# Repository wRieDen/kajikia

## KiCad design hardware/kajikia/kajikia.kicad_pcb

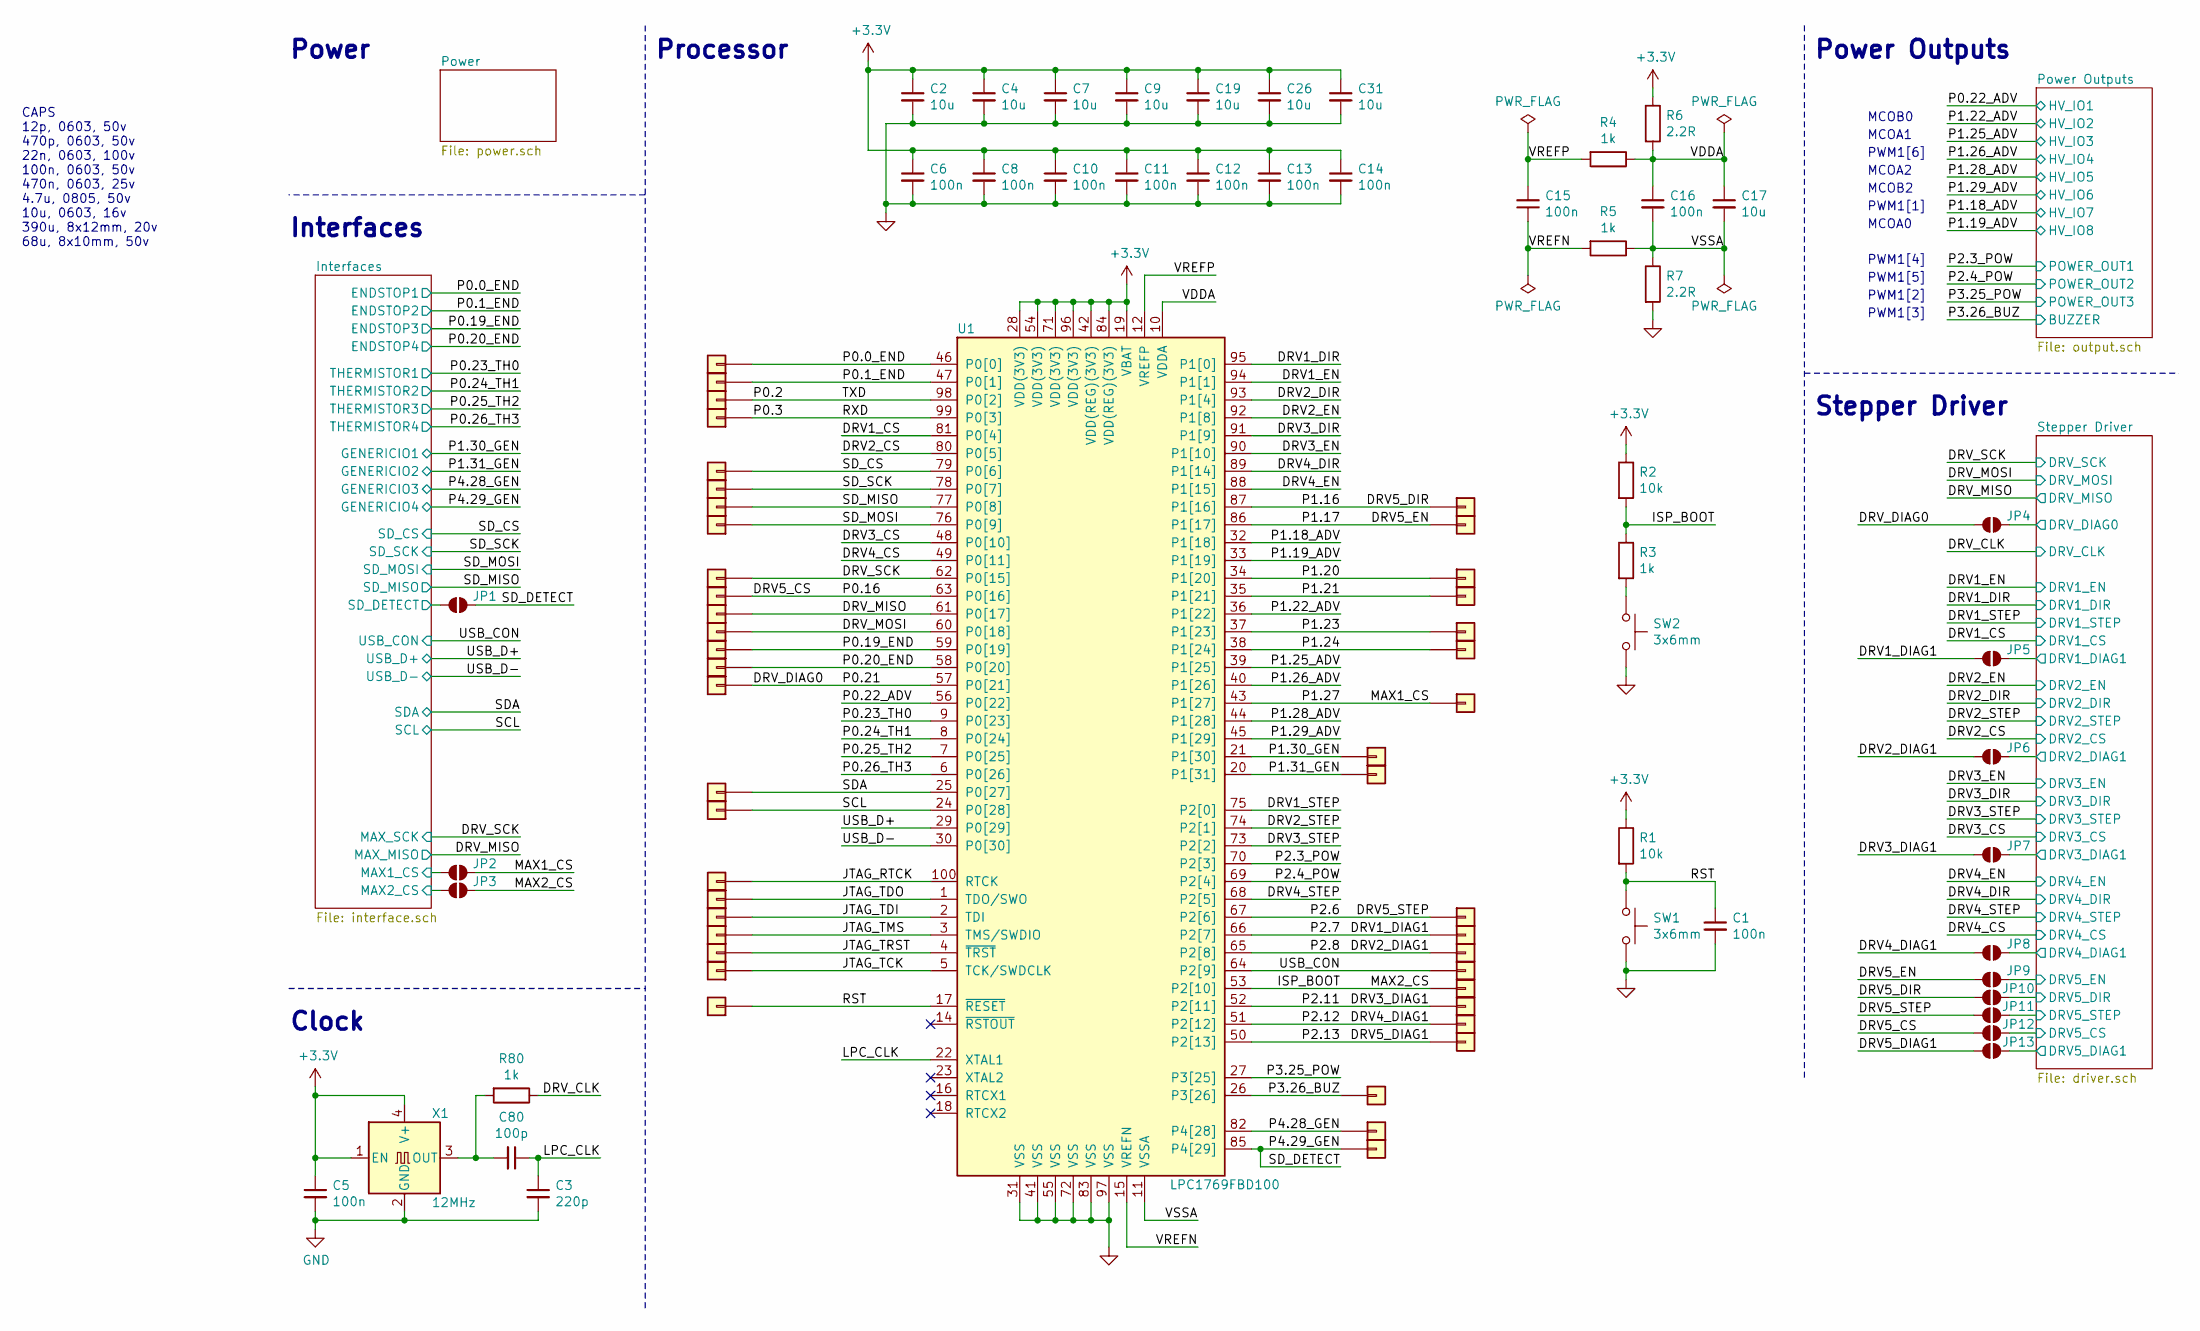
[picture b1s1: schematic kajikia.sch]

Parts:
C1, C5, C6, C8, C10, C11, C12, C13, C14, C15, C16: 100n; 0603_CAP
C2, C4, C7, C9, C17, C19, C26, C31: 10u; 0603_CAP
C3: 220p; 0603_CAP
C80: 100p; 0603_CAP
J1, J2, J3, J4, J5, J6, J7, J8, J9, J10, J11, J12, J13, J14, J15, J16, J17, J18, J19, J20, J21, J22, J23, J24, J25, J26, J27, J28, J29, J30, J31, J32, J33, J34, J35, J36, J37, J38, J52, J75, J76, J77, J78, J104: Conn_01x01; PinHeader_2.54mm_1P
JP1, JP2, JP3, JP4, JP5, JP6, JP7, JP8, JP9, JP10, JP11, JP12, JP13: SolderJumper_2_Open; Solder Jumper 2P
R1, R2: 10k; 0603_RES
R3, R4, R5, R80: 1k; 0603_RES
R6, R7: 2.2R; 0603_RES
SW1, SW2: 3x6mm; Switch_3x4mm
U1: LPC1769FBD100; LQFP-100_14x14mm_P0.5mm
X1: 12MHz; Oscillator_SMD_EuroQuartz_XO32-4Pin_3.2x2.5mm

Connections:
+3V3: C2.1, C4.1, C5.1, C6.1, C7.1, C8.1, C9.1, C10.1, C11.1, C12.1, C13.1, C14.1, C19.1, C26.1, C31.1, R1.1, R2.1, R6.1, U1.19 (VBAT), U1.28 (VDD(3V3)), U1.42 (VDD(REG)(3V3)), U1.54 (VDD(3V3)), U1.71 (VDD(3V3)), U1.84 (VDD(REG)(3V3)), U1.96 (VDD(3V3)), X1.1 (EN), X1.4 (V+); also elsewhere on the board
/DRV1_CS: U1.81 (P0[4]); also elsewhere on the board
/DRV1_DIAG1: J33.1, JP5.1 (A), U1.66 (P2[7])
/DRV1_DIR: U1.95 (P1[0]); also elsewhere on the board
/DRV1_EN: U1.94 (P1[1]); also elsewhere on the board
/DRV1_STEP: U1.75 (P2[0]); also elsewhere on the board
/DRV2_CS: U1.80 (P0[5]); also elsewhere on the board
/DRV2_DIAG1: J34.1, JP6.1 (A), U1.65 (P2[8])
/DRV2_DIR: U1.93 (P1[4]); also elsewhere on the board
/DRV2_EN: U1.92 (P1[8]); also elsewhere on the board
/DRV2_STEP: U1.74 (P2[1]); also elsewhere on the board
/DRV3_CS: U1.48 (P0[10]); also elsewhere on the board
/DRV3_DIAG1: J36.1, JP7.1 (A), U1.52 (P2[11])
/DRV3_DIR: U1.91 (P1[9]); also elsewhere on the board
/DRV3_EN: U1.90 (P1[10]); also elsewhere on the board
/DRV3_STEP: U1.73 (P2[2]); also elsewhere on the board
/DRV4_CS: U1.49 (P0[11]); also elsewhere on the board
/DRV4_DIAG1: J37.1, JP8.1 (A), U1.51 (P2[12])
/DRV4_DIR: U1.89 (P1[14]); also elsewhere on the board
/DRV4_EN: U1.88 (P1[15]); also elsewhere on the board
/DRV4_STEP: U1.68 (P2[5]); also elsewhere on the board
/DRV5_CS: J10.1, JP12.1 (A), U1.63 (P0[16])
/DRV5_DIAG1: J38.1, JP13.1 (A), U1.50 (P2[13])
/DRV5_DIR: J25.1, JP10.1 (A), U1.87 (P1[16])
/DRV5_EN: J26.1, JP9.1 (A), U1.86 (P1[17])
/DRV5_STEP: J32.1, JP11.1 (A), U1.67 (P2[6])
/DRV_CLK: R80.1; also elsewhere on the board
/DRV_DIAG0: J15.1, JP4.1 (A), U1.57 (P0[21])
/DRV_MISO: J11.1, U1.61 (P0[17]); also elsewhere on the board
/DRV_MOSI: J12.1, U1.60 (P0[18]); also elsewhere on the board
/DRV_SCK: J9.1, U1.62 (P0[15]); also elsewhere on the board
/ISP_BOOT: J35.1, JP3.2 (B), R2.2, R3.1, U1.53 (P2[10])
/Interfaces/MAX1_CS: JP2.1 (A); also elsewhere on the board
/Interfaces/MAX2_CS: JP3.1 (A); also elsewhere on the board
/Interfaces/SD_DETECT: JP1.1 (A); also elsewhere on the board
/JTAG_RTCK: J18.1, U1.100 (RTCK)
/JTAG_TCK: J23.1, U1.5 (TCK/SWDCLK)
/JTAG_TDI: J20.1, U1.2 (TDI)
/JTAG_TDO: J19.1, U1.1 (TDO/SWO)
/JTAG_TMS: J21.1, U1.3 (TMS/SWDIO)
/JTAG_TRST: J22.1, U1.4 (~TRST~)
/LPC_CLK: C3.1, C80.1, U1.22 (XTAL1)
/MAX1_CS: J31.1, JP2.2 (B), U1.43 (P1[27])
/P0.0_END: J1.1, U1.46 (P0[0]); also elsewhere on the board
/P0.1_END: J2.1, U1.47 (P0[1]); also elsewhere on the board
/P0.2: J3.1, U1.98 (P0[2])
/P0.3: J4.1, U1.99 (P0[3])
/P0.19_END: J13.1, U1.59 (P0[19]); also elsewhere on the board
/P0.20_END: J14.1, U1.58 (P0[20]); also elsewhere on the board
/P0.22_ADV: U1.56 (P0[22]); also elsewhere on the board
/P0.23_TH0: U1.9 (P0[23]); also elsewhere on the board
/P0.24_TH1: U1.8 (P0[24]); also elsewhere on the board
/P0.25_TH2: U1.7 (P0[25]); also elsewhere on the board
/P0.26_TH3: U1.6 (P0[26]); also elsewhere on the board
/P1.18_ADV: U1.32 (P1[18]); also elsewhere on the board
/P1.19_ADV: U1.33 (P1[19]); also elsewhere on the board
/P1.20: J27.1, U1.34 (P1[20])
/P1.21: J28.1, U1.35 (P1[21])
/P1.22_ADV: U1.36 (P1[22]); also elsewhere on the board
/P1.23: J29.1, U1.37 (P1[23])
/P1.24: J30.1, U1.38 (P1[24])
/P1.25_ADV: U1.39 (P1[25]); also elsewhere on the board
/P1.26_ADV: U1.40 (P1[26]); also elsewhere on the board
/P1.28_ADV: U1.44 (P1[28]); also elsewhere on the board
/P1.29_ADV: U1.45 (P1[29]); also elsewhere on the board
/P1.30_GEN: J75.1, U1.21 (P1[30])
/P1.31_GEN: J76.1, U1.20 (P1[31])
/P2.3_POW: U1.70 (P2[3]); also elsewhere on the board
/P2.4_POW: U1.69 (P2[4]); also elsewhere on the board
/P3.25_POW: U1.27 (P3[25]); also elsewhere on the board
/P3.26_BUZ: J104.1, U1.26 (P3[26]); also elsewhere on the board
/P4.28_GEN: J77.1, U1.82 (P4[28])
/P4.29_GEN: J78.1, JP1.2 (B), U1.85 (P4[29])
/RST: C1.1, J24.1, R1.2, SW1.1, U1.17 (~RESET~); also elsewhere on the board
/SCL: J17.1, U1.24 (P0[28]); also elsewhere on the board
/SDA: J16.1, U1.25 (P0[27]); also elsewhere on the board
/SD_CS: J5.1, U1.79 (P0[6]); also elsewhere on the board
/SD_MISO: J7.1, U1.77 (P0[8]); also elsewhere on the board
/SD_MOSI: J8.1, U1.76 (P0[9]); also elsewhere on the board
/SD_SCK: J6.1, U1.78 (P0[7]); also elsewhere on the board
/Stepper Driver/DRV1_DIAG1: JP5.2 (B); also elsewhere on the board
/Stepper Driver/DRV2_DIAG1: JP6.2 (B); also elsewhere on the board
/Stepper Driver/DRV3_DIAG1: JP7.2 (B); also elsewhere on the board
/Stepper Driver/DRV4_DIAG1: JP8.2 (B); also elsewhere on the board
/Stepper Driver/DRV5_CS: JP12.2 (B); also elsewhere on the board
/Stepper Driver/DRV5_DIAG1: JP13.2 (B); also elsewhere on the board
/Stepper Driver/DRV5_DIR: JP10.2 (B); also elsewhere on the board
/Stepper Driver/DRV5_EN: JP9.2 (B); also elsewhere on the board
/Stepper Driver/DRV5_STEP: JP11.2 (B); also elsewhere on the board
/Stepper Driver/DRV_DIAG0: JP4.2 (B); also elsewhere on the board
/USB_CON: J52.1, U1.64 (P2[9]); also elsewhere on the board
/USB_D+: U1.29 (P0[29]); also elsewhere on the board
/USB_D-: U1.30 (P0[30]); also elsewhere on the board
/VDDA: C16.1, C17.1, R4.1, R6.2, U1.10 (VDDA)
/VREFN: C15.1, R5.2, U1.15 (VREFN)
/VREFP: C15.2, R4.2, U1.12 (VREFP)
/VSSA: C16.2, C17.2, R5.1, R7.1, U1.11 (VSSA)
GND: C1.2, C2.2, C3.2, C4.2, C5.2, C6.2, C7.2, C8.2, C9.2, C10.2, C11.2, C12.2, C13.2, C14.2, C19.2, C26.2, C31.2, R7.2, SW1.2, SW2.2, U1.31 (VSS), U1.41 (VSS), U1.55 (VSS), U1.72 (VSS), U1.83 (VSS), U1.97 (VSS), X1.2 (GND); also elsewhere on the board
unnamed: C80.2, R80.2, X1.3 (OUT)
unnamed 328: R3.2, SW2.1; also elsewhere on the board

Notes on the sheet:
CAPS 12p, 0603, 50v 470p, 0603, 50v 22n, 0603, 100v 100n, 0603, 50v 470n, 0603, 25v 4.7u, 0805, 50v 10u, 0603, 16v 390u, 8x12mm, 20v 68u, 8x10mm, 50v
Power
Interfaces
Processor
Power Outputs
Stepper Driver
PWM1[3]
PWM1[6]
MCOA1
MCOA2
MCOB2
PWM1[2]
PWM1[5]
PWM1[4]
MCOB0
PWM1[1]
MCOA0
Clock

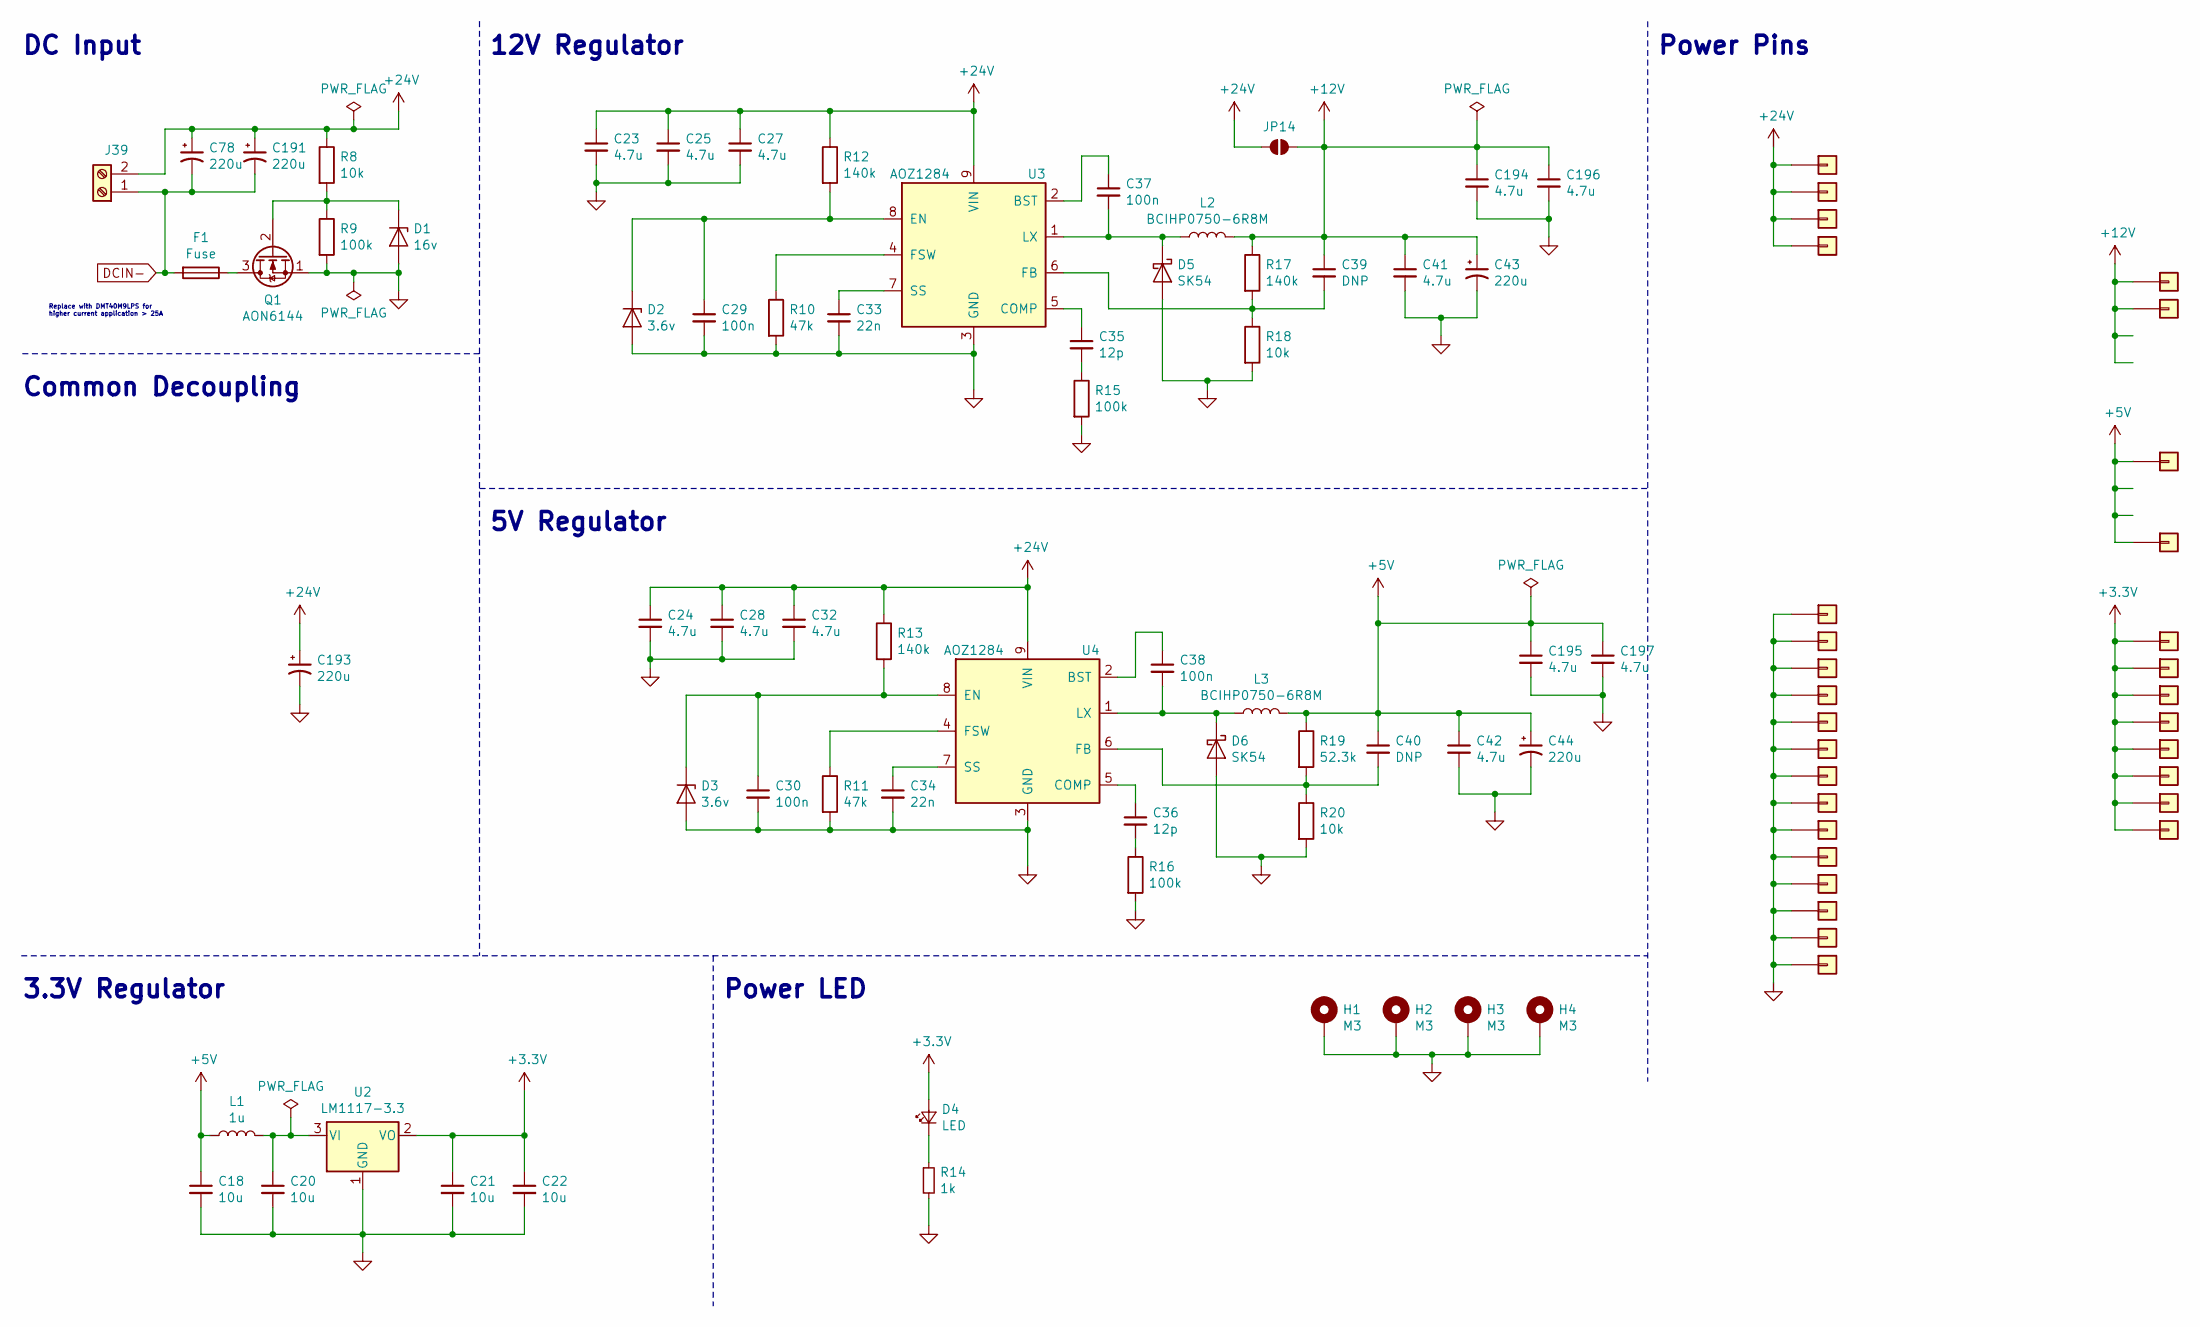
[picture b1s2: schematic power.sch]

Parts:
C18, C20, C21, C22: 10u; 0603_CAP
C23, C24, C25, C27, C28, C32, C41, C42, C194, C195, C196, C197: 4.7u; 1210_CAP
C29, C30, C37, C38: 100n; 0603_CAP
C33, C34: 22n; 0603_CAP
C35, C36: 12p; 0603_CAP
C39, C40: DNP; 0603_CAP
C43, C44, C78, C191, C193: 220u; CP_Elec_6.3x7.7
D1: 16v; SOD-523_DIODE
D2, D3: 3.6v; SOD-523_DIODE
D4: LED; 0603_LED
D5, D6: SK54; SMB_DIODE
F1: Fuse; SMD_Fuseholder
H1, H2, H3, H4: M3; MountingHole_3.2mm_M3_ISO14580_Pad
J39: Screw_Terminal_01x02; KF635-2P
J40, J41, J42, J43, J44, J45, J48, J49, J50, J51, J53, J54, J55, J56, J57, J58, J59, J68, J69, J70, J94, J95, J96, J97, J98, J99, J100, J101, J102, J103: Conn_01x01; PinHeader_2.54mm_1P
JP14: SolderJumper_2_Open; Solder Jumper 2P
L1: 1u; 0805_IND
L2, L3: BCIHP0750-6R8M; 7x7mm_IND
Q1: AON6144; DFN5x6-8
R8, R18, R20: 10k; 0603_RES
R9, R15, R16: 100k; 0603_RES
R10, R11: 47k; 0603_RES
R12, R13, R17: 140k; 0603_RES
R14: 1k; 0603_RES
R19: 52.3k; 0603_RES
U2: LM1117-3.3; SOT-223-3_TabPin2
U3, U4: AOZ1284; SO-8-EP1

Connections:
+3V3: C21.1, C22.1, D4.2 (A), J54.1, J55.1, J94.1, J95.1, J100.1, J101.1, J102.1, J103.1, U2.2 (VO); also elsewhere on the board
+5V: C18.1, C40.1, C42.1, C44.1, C195.1, C197.1, J48.1, J51.1, L1.1, L3.2, R19.1; also elsewhere on the board
+12V: C39.1, C41.1, C43.1, C194.1, C196.1, J44.1, J45.1, JP14.2 (B), L2.2, R17.1; also elsewhere on the board
+24V: C23.1, C24.1, C25.1, C27.1, C28.1, C32.1, C78.1, C191.1, C193.1, J39.2, J40.1, J41.1, J42.1, J43.1, JP14.1 (A), R8.1, R12.1, R13.1, U3.9 (VIN), U4.9 (VIN); also elsewhere on the board
DCIN-: C78.2, C191.2, F1.2, J39.1; also elsewhere on the board
GND: C18.2, C20.2, C21.2, C22.2, C23.2, C24.2, C25.2, C27.2, C28.2, C29.2, C30.2, C32.2, C33.2, C34.2, C41.2, C42.2, C43.2, C44.2, C193.2, C194.2, C195.2, C196.2, C197.2, D1.2 (A), D2.2 (A), D3.2 (A), D5.2 (A), D6.2 (A), H1.1, H2.1, H3.1, H4.1, J49.1, J50.1, J53.1, J56.1, J57.1, J58.1, J59.1, J68.1, J69.1, J70.1, J96.1, J97.1, J98.1, J99.1, Q1.1 (S), R9.2, R10.2, R11.2, R14.2, R15.2, R16.2, R18.2, R20.2, U2.1 (GND), U3.3 (GND), U4.3 (GND); also elsewhere on the board
unnamed: C20.1, L1.2, U2.3 (VI)
unnamed: C29.1, D2.1 (K), R12.2, U3.8 (EN)
unnamed: C30.1, D3.1 (K), R13.2, U4.8 (EN)
unnamed: C33.1, U3.7 (SS)
unnamed: C34.1, U4.7 (SS)
unnamed: C35.1, U3.5 (COMP)
unnamed: C35.2, R15.1
unnamed: C36.1, U4.5 (COMP)
unnamed: C36.2, R16.1
unnamed: C37.1, U3.2 (BST)
unnamed: C37.2, D5.1 (K), L2.1, U3.1 (LX)
unnamed: C38.1, U4.2 (BST)
unnamed: C38.2, D6.1 (K), L3.1, U4.1 (LX)
unnamed: C39.2, R17.2, R18.1, U3.6 (FB)
unnamed: C40.2, R19.2, R20.1, U4.6 (FB)
unnamed: D1.1 (K), Q1.2 (G), R8.2, R9.1
unnamed: D4.1 (K), R14.1
unnamed: F1.1, Q1.3 (D)
unnamed: R10.1, U3.4 (FSW)
unnamed: R11.1, U4.4 (FSW)

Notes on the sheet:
3.3V Regulator
5V Regulator
12V Regulator
DC Input
Power Pins
Common Decoupling
Power LED
Replace with DMT40M9LPS for higher current application > 25A

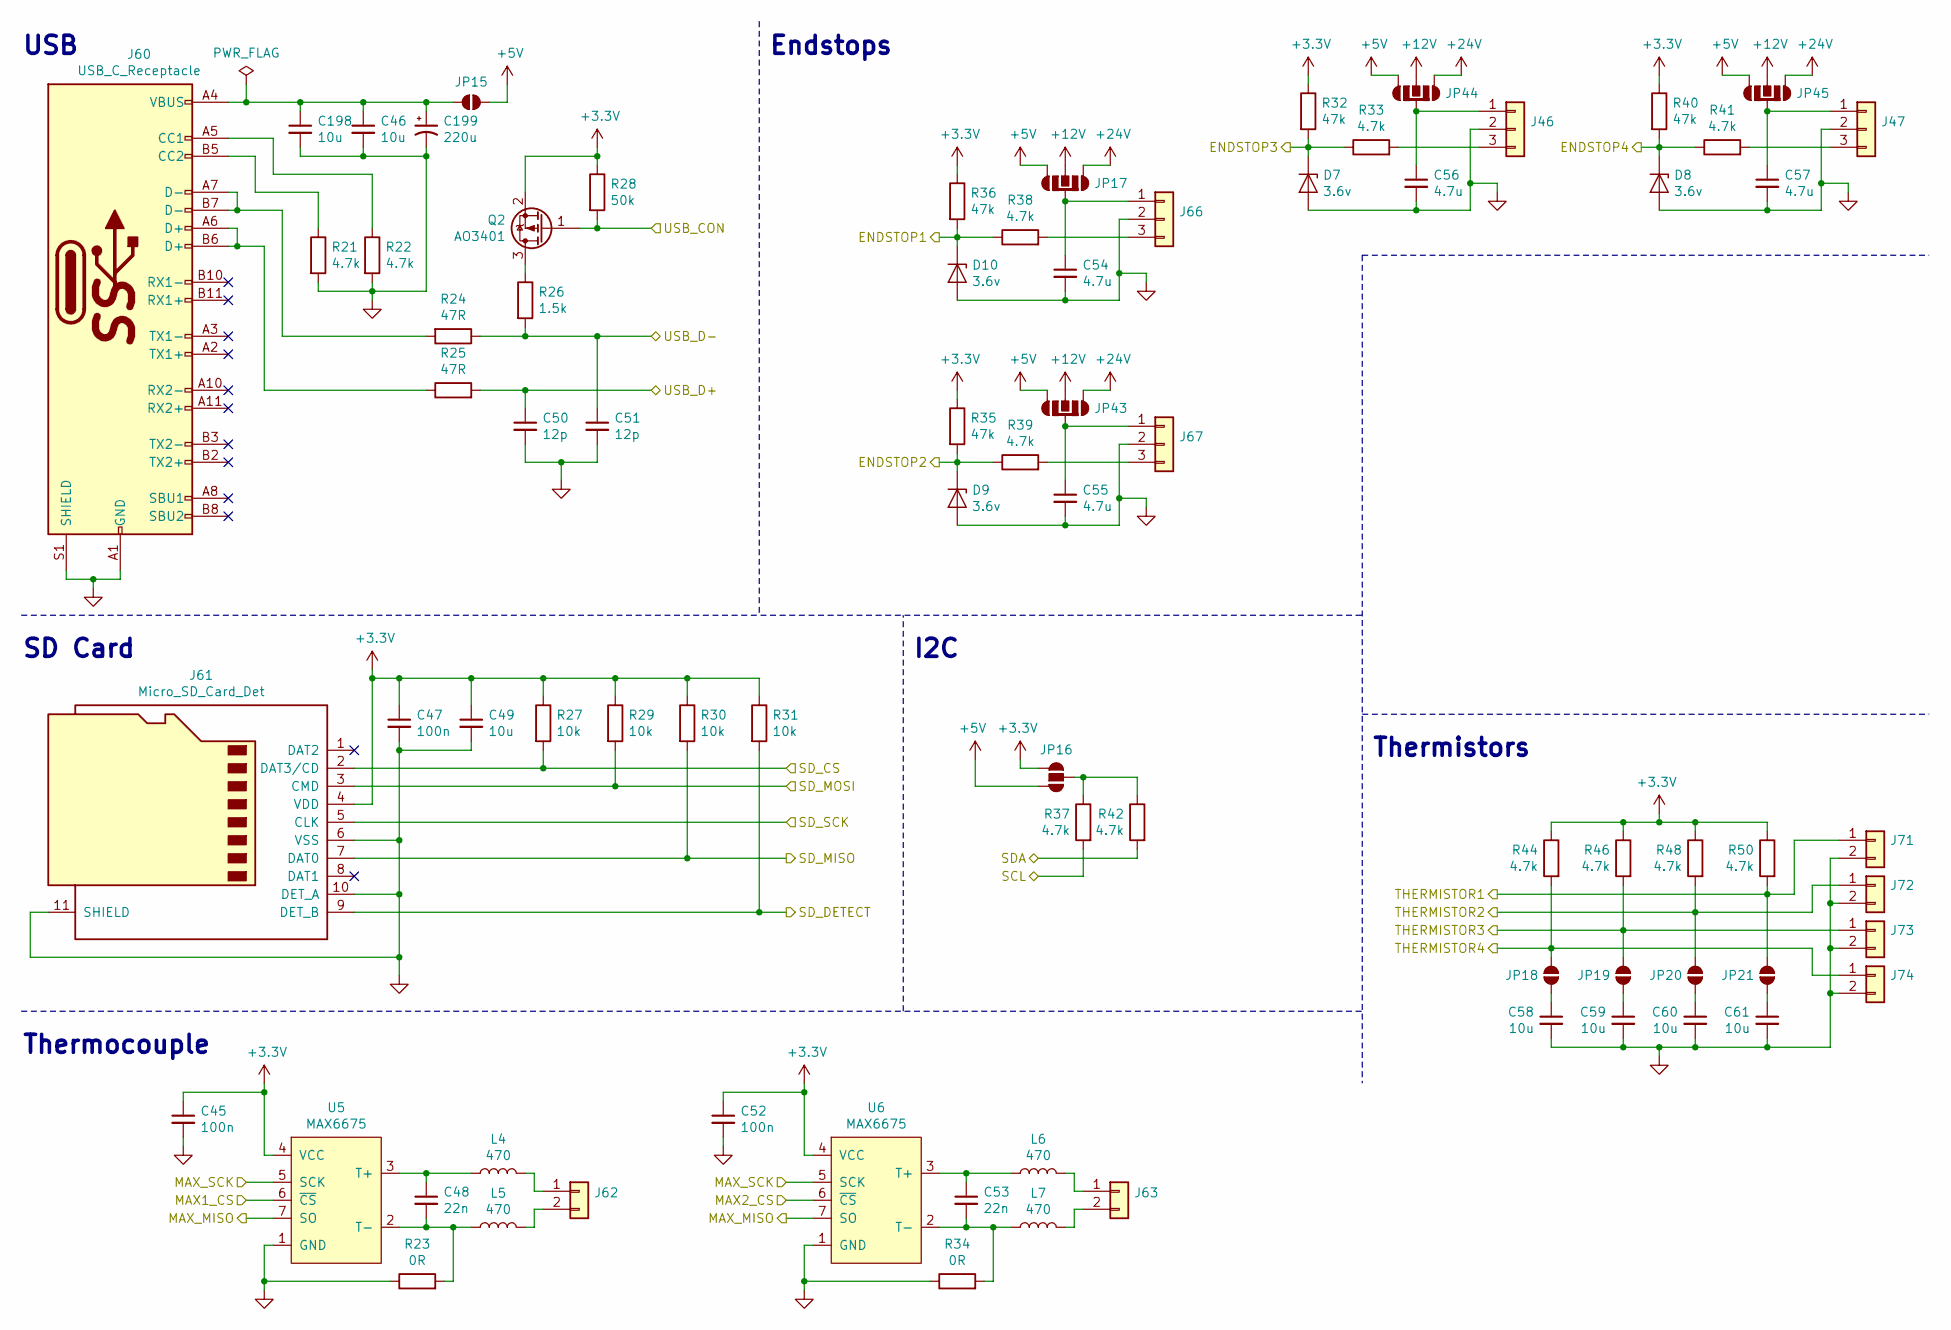
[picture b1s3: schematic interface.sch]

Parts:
C45, C47, C52: 100n; 0603_CAP
C46, C49, C58, C59, C60, C61, C198: 10u; 0603_CAP
C48, C53: 22n; 0603_CAP
C50, C51: 12p; 0603_CAP
C54, C55, C56, C57: 4.7u; 0805_CAP
C199: 220u; CP_Elec_6.3x7.7
D7, D8, D9, D10: 3.6v; SOD-523_DIODE
J46, J47, J66, J67: Conn_01x03; JST_XH_3P
J60: USB_C_Receptacle; TYPE-C-31-M-12
J61: Micro_SD_Card_Det; HYC77-TF09-200
J62, J63, J71, J72, J73, J74: Conn_01x02; JST_XH_2P
JP15, JP18, JP19, JP20, JP21: SolderJumper_2_Open; Solder Jumper 2P
JP16: SolderJumper_3_Open; Solder Jumper 3P
JP17, JP43, JP44, JP45: SolderJumper_4_Open; SolderJumper_JST
L4, L5, L6, L7: 470; 0603_IND
Q2: AO3401; SOT-23
R21, R22, R33, R37, R38, R39, R41, R42, R44, R46, R48, R50: 4.7k; 0603_RES
R23, R34: 0R; 0603_RES
R24, R25: 47R; 0603_RES
R26: 1.5k; 0603_RES
R27, R29, R30, R31: 10k; 0603_RES
R28: 50k; 0603_RES
R32, R35, R36, R40: 47k; 0603_RES
U5, U6: MAX6675; SO-8

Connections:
+3V3: C45.1, C47.1, C49.1, C52.1, J61.4 (VDD), JP16.3 (B), Q2.2 (S), R27.1, R28.1, R29.1, R30.1, R31.1, R32.1, R35.1, R36.1, R40.1, R44.1, R46.1, R48.1, R50.1, U5.4 (VCC), U6.4 (VCC); also elsewhere on the board
+5V: JP15.2 (B), JP16.1 (A), JP17.2 (O1), JP43.2 (O1), JP44.2 (O1), JP45.2 (O1); also elsewhere on the board
+12V: JP17.3 (O2), JP43.3 (O2), JP44.3 (O2), JP45.3 (O2); also elsewhere on the board
+24V: JP17.4 (O4), JP43.4 (O4), JP44.4 (O4), JP45.4 (O4); also elsewhere on the board
/DRV_MISO: U5.7 (SO), U6.7 (SO); also elsewhere on the board
/DRV_SCK: U5.5 (SCK), U6.5 (SCK); also elsewhere on the board
/Interfaces/MAX1_CS: U5.6 (~CS); also elsewhere on the board
/Interfaces/MAX2_CS: U6.6 (~CS); also elsewhere on the board
/Interfaces/SD_DETECT: J61.9 (DET_B), R31.2; also elsewhere on the board
/P0.0_END: D10.1 (K), R36.2, R38.1; also elsewhere on the board
/P0.1_END: D9.1 (K), R35.2, R39.1; also elsewhere on the board
/P0.19_END: D7.1 (K), R32.2, R33.1; also elsewhere on the board
/P0.20_END: D8.1 (K), R40.2, R41.1; also elsewhere on the board
/P0.23_TH0: J71.1, JP21.1 (A), R50.2; also elsewhere on the board
/P0.24_TH1: J72.1, JP20.1 (A), R48.2; also elsewhere on the board
/P0.25_TH2: J73.1, JP19.1 (A), R46.2; also elsewhere on the board
/P0.26_TH3: J74.1, JP18.1 (A), R44.2; also elsewhere on the board
/SCL: R37.2; also elsewhere on the board
/SDA: R42.2; also elsewhere on the board
/SD_CS: J61.2 (DAT3/CD), R27.2; also elsewhere on the board
/SD_MISO: J61.7 (DAT0), R30.2; also elsewhere on the board
/SD_MOSI: J61.3 (CMD), R29.2; also elsewhere on the board
/SD_SCK: J61.5 (CLK); also elsewhere on the board
/USB_CON: Q2.1 (G), R28.2; also elsewhere on the board
/USB_D+: C50.1, R25.2; also elsewhere on the board
/USB_D-: C51.1, R24.1, R26.2; also elsewhere on the board
GND: C45.2, C46.2, C47.2, C49.2, C50.2, C51.2, C52.2, C54.2, C55.2, C56.2, C57.2, C58.2, C59.2, C60.2, C61.2, C198.2, C199.2, D7.2 (A), D8.2 (A), D9.2 (A), D10.2 (A), J46.2, J47.2, J60.A1 (GND), J60.A12 (GND), J60.B1 (GND), J60.B12 (GND), J60.S1 (SHIELD), J61.6 (VSS), J61.10 (DET_A), J61.11 (SHIELD), J66.2, J67.2, J71.2, J72.2, J73.2, J74.2, R21.2, R22.2, R23.1, R34.1, U5.1 (GND), U6.1 (GND); also elsewhere on the board
unnamed: C48.1, L4.1, U5.3 (T+)
unnamed: C48.2, L5.1, R23.2, U5.2 (T-)
unnamed: C53.1, L6.1, U6.3 (T+)
unnamed: C53.2, L7.1, R34.2, U6.2 (T-)
unnamed: C54.1, J66.1, JP17.1 (IN)
unnamed: C55.1, J67.1, JP43.1 (IN)
unnamed: C56.1, J46.1, JP44.1 (IN)
unnamed: C57.1, J47.1, JP45.1 (IN)
unnamed: C58.1, JP18.2 (B)
unnamed: C59.1, JP19.2 (B)
unnamed: C60.1, JP20.2 (B)
unnamed: C61.1, JP21.2 (B)
unnamed: J46.3, R33.2
unnamed: J47.3, R41.2
unnamed: J60.A5 (CC1), R22.1
unnamed: J60.A6 (D+), J60.B6 (D+), R25.1
unnamed: J60.A7 (D-), J60.B7 (D-), R24.2
unnamed: J60.B5 (CC2), R21.1
unnamed: J62.1, L4.2
unnamed: J62.2, L5.2
unnamed: J63.1, L6.2
unnamed: J63.2, L7.2
unnamed: J66.3, R38.2
unnamed: J67.3, R39.2
unnamed: JP16.2 (C), R37.1, R42.1
unnamed: Q2.3 (D), R26.1
VBUS: C46.1, C198.1, C199.1, J60.A4 (VBUS), J60.A9 (VBUS), J60.B4 (VBUS), J60.B9 (VBUS), JP15.1 (A)

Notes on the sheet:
USB
SD Card
Thermocouple
Endstops
Thermistors
I2C

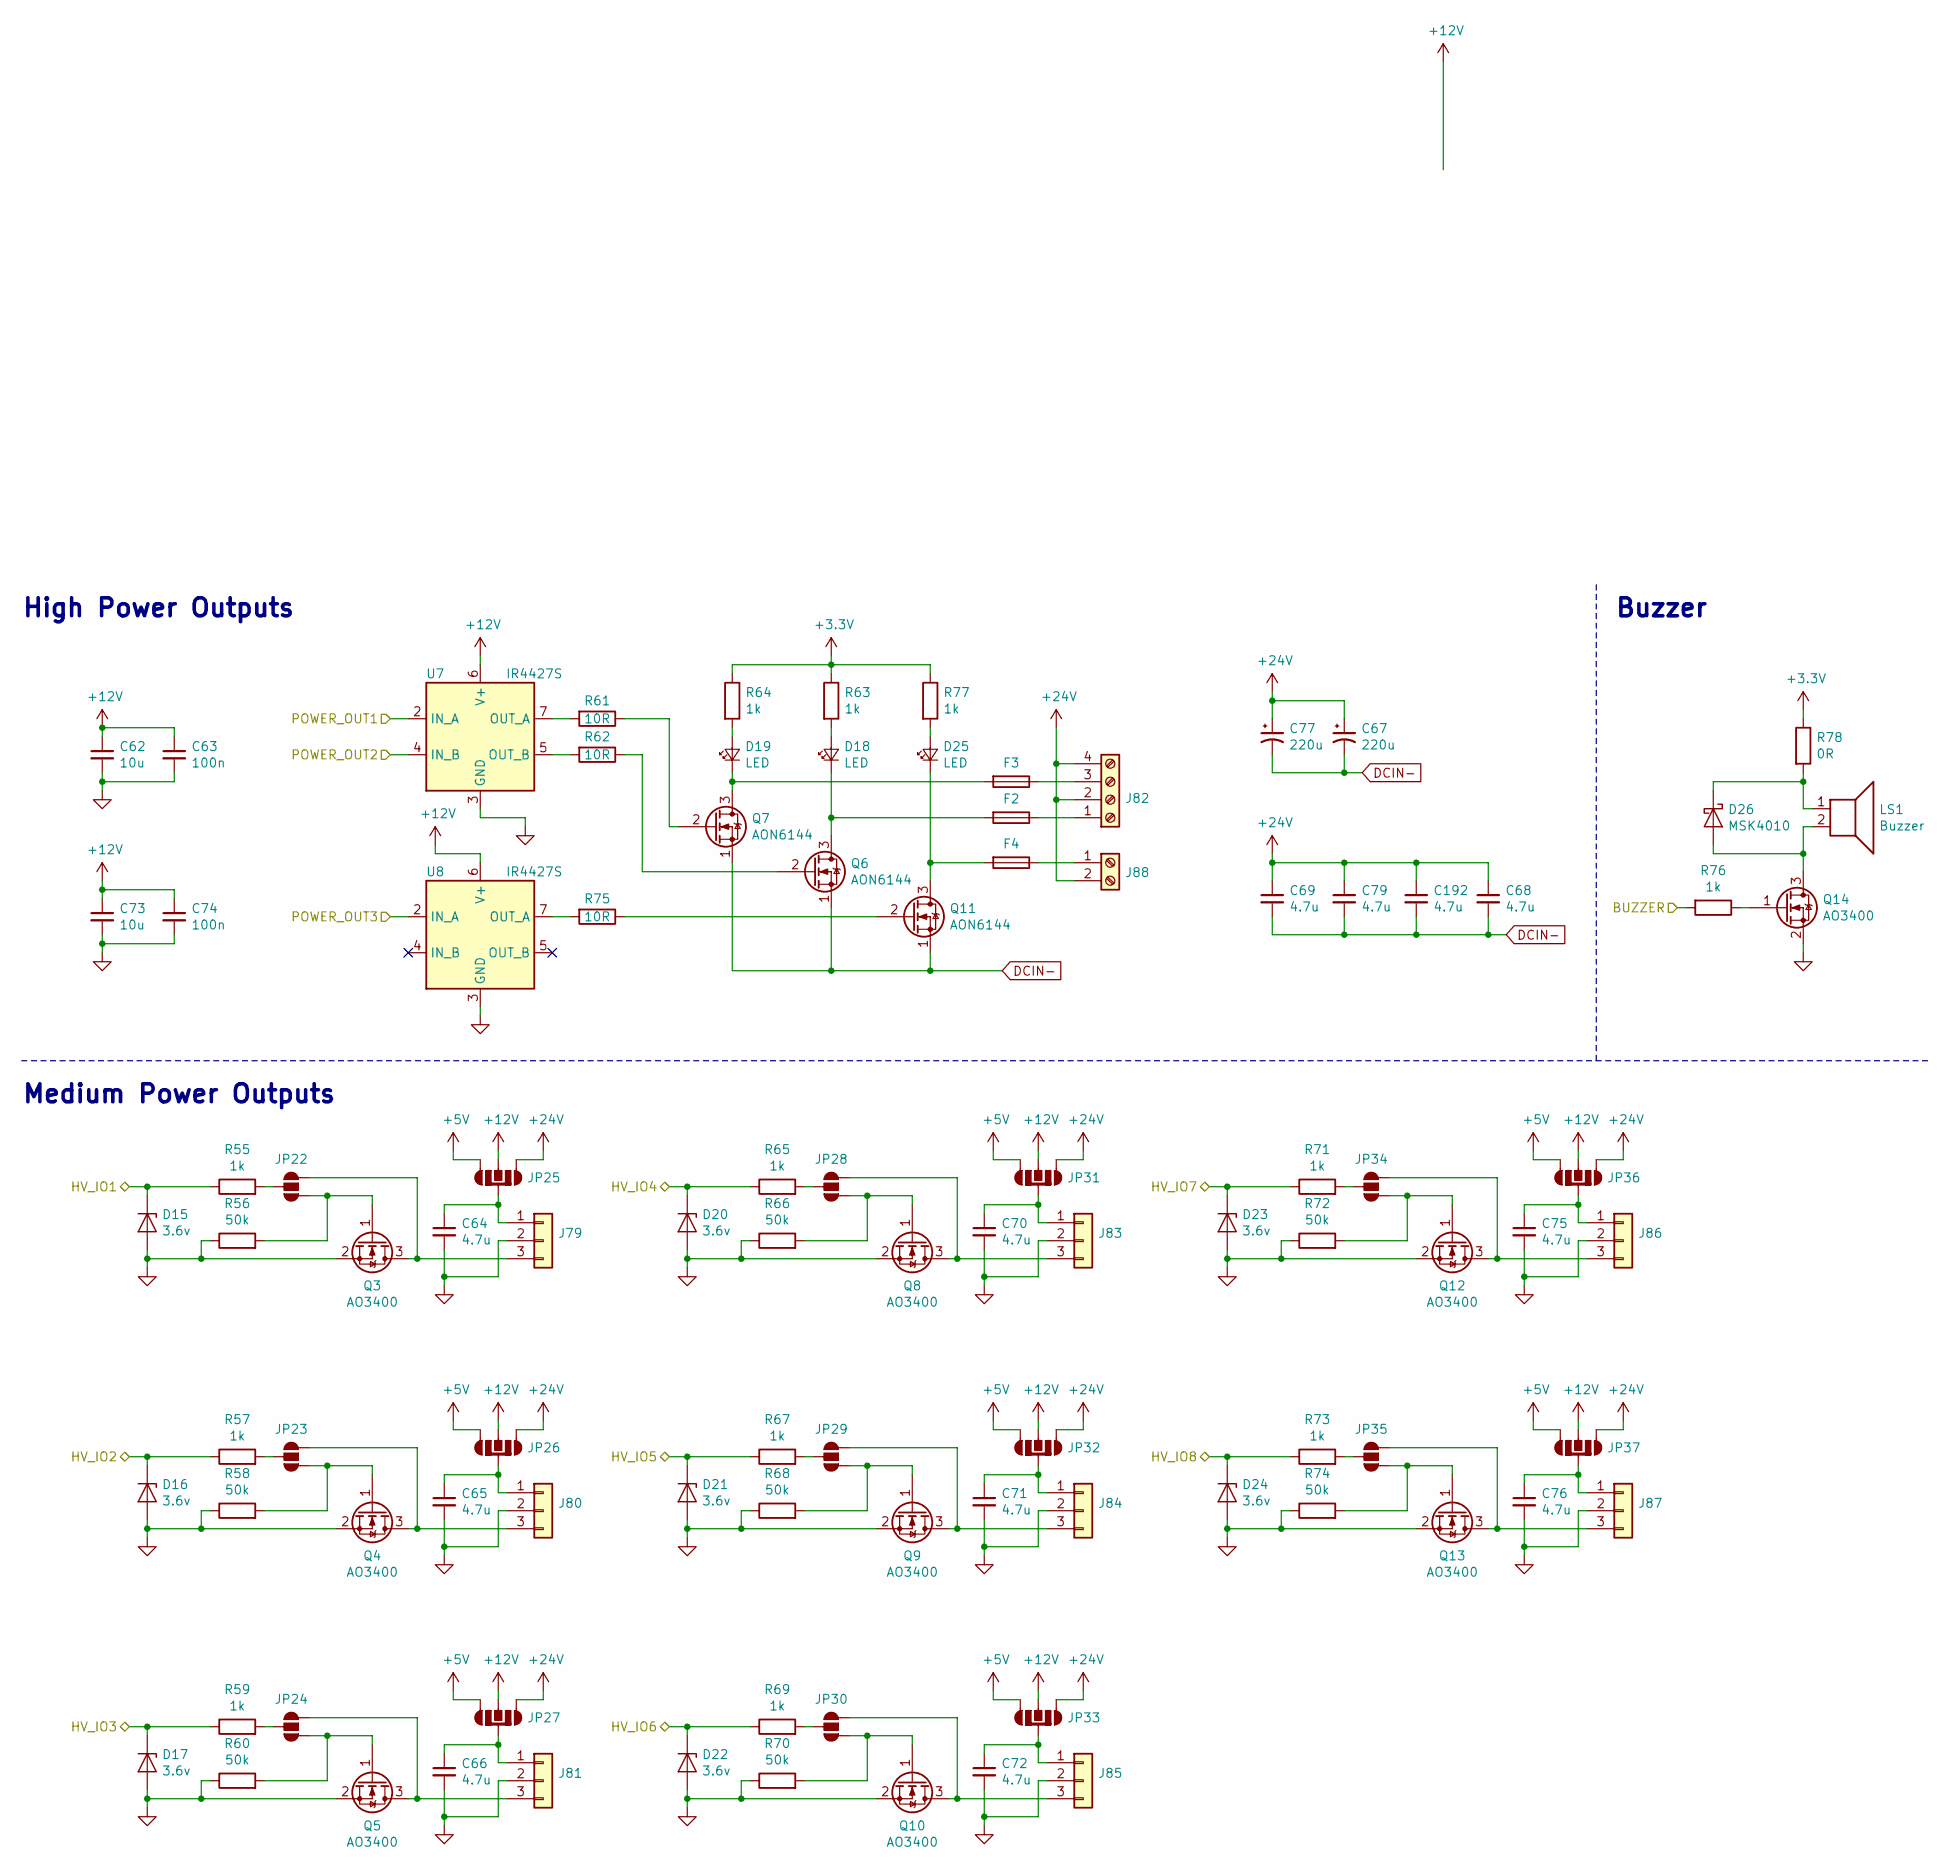
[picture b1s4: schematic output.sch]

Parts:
C62, C73: 10u; 0603_CAP
C63, C74: 100n; 0603_CAP
C64, C65, C66, C70, C71, C72, C75, C76: 4.7u; 0805_CAP
C67, C77: 220u; CP_Elec_6.3x7.7
C68, C69, C79, C192: 4.7u; 1210_CAP
D15, D16, D17, D20, D21, D22, D23, D24: 3.6v; SOD-523_DIODE
D18, D19, D25: LED; 0603_LED
D26: MSK4010; SOD-523_DIODE
F2, F3, F4: Fuse; SMD_Fuseholder
J79, J80, J81, J83, J84, J85, J86, J87: Conn_01x03; JST_XH_3P
J82: Screw_Terminal_01x04; KF635-4P
J88: Screw_Terminal_01x02; KF635-2P
JP22, JP23, JP24, JP28, JP29, JP30, JP34, JP35: SolderJumper_3_Open; Solder Jumper 3P
JP25, JP26, JP27, JP31, JP32, JP33, JP36, JP37: SolderJumper_4_Open; SolderJumper_JST
LS1: Buzzer; Buzzer-7525
Q3, Q4, Q5, Q8, Q9, Q10, Q12, Q13, Q14: AO3400; SOT-23
Q6, Q7, Q11: AON6144; DFN5x6-8
R55, R57, R59, R63, R64, R65, R67, R69, R71, R73, R76, R77: 1k; 0603_RES
R56, R58, R60, R66, R68, R70, R72, R74: 50k; 0603_RES
R61, R62, R75: 10R; 0603_RES
R78: 0R; 0603_RES
U7, U8: IR4427S; SO-8

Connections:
+3V3: R63.1, R64.1, R77.1, R78.1; also elsewhere on the board
+5V: JP25.2 (O1), JP26.2 (O1), JP27.2 (O1), JP31.2 (O1), JP32.2 (O1), JP33.2 (O1), JP36.2 (O1), JP37.2 (O1); also elsewhere on the board
+12V: C62.1, C63.1, C73.1, C74.1, JP25.3 (O2), JP26.3 (O2), JP27.3 (O2), JP31.3 (O2), JP32.3 (O2), JP33.3 (O2), JP36.3 (O2), JP37.3 (O2), U7.6 (V+), U8.6 (V+); also elsewhere on the board
+24V: C67.1, C68.1, C69.1, C77.1, C79.1, C192.1, J82.2, J82.4, J88.2, JP25.4 (O4), JP26.4 (O4), JP27.4 (O4), JP31.4 (O4), JP32.4 (O4), JP33.4 (O4), JP36.4 (O4), JP37.4 (O4); also elsewhere on the board
/P0.22_ADV: D15.1 (K), R55.1; also elsewhere on the board
/P1.18_ADV: D23.1 (K), R71.1; also elsewhere on the board
/P1.19_ADV: D24.1 (K), R73.1; also elsewhere on the board
/P1.22_ADV: D16.1 (K), R57.1; also elsewhere on the board
/P1.25_ADV: D17.1 (K), R59.1; also elsewhere on the board
/P1.26_ADV: D20.1 (K), R65.1; also elsewhere on the board
/P1.28_ADV: D21.1 (K), R67.1; also elsewhere on the board
/P1.29_ADV: D22.1 (K), R69.1; also elsewhere on the board
/P2.3_POW: U7.2 (IN_A); also elsewhere on the board
/P2.4_POW: U7.4 (IN_B); also elsewhere on the board
/P3.25_POW: U8.2 (IN_A); also elsewhere on the board
/P3.26_BUZ: R76.2; also elsewhere on the board
DCIN-: C67.2, C68.2, C69.2, C77.2, C79.2, C192.2, Q6.1 (S), Q7.1 (S), Q11.1 (S); also elsewhere on the board
GND: C62.2, C63.2, C64.2, C65.2, C66.2, C70.2, C71.2, C72.2, C73.2, C74.2, C75.2, C76.2, D15.2 (A), D16.2 (A), D17.2 (A), D20.2 (A), D21.2 (A), D22.2 (A), D23.2 (A), D24.2 (A), J79.2, J80.2, J81.2, J83.2, J84.2, J85.2, J86.2, J87.2, Q3.2 (S), Q4.2 (S), Q5.2 (S), Q8.2 (S), Q9.2 (S), Q10.2 (S), Q12.2 (S), Q13.2 (S), Q14.2 (S), R56.1, R58.1, R60.1, R66.1, R68.1, R70.1, R72.1, R74.1, U7.3 (GND), U8.3 (GND); also elsewhere on the board
unnamed: C64.1, J79.1, JP25.1 (IN)
unnamed: C65.1, J80.1, JP26.1 (IN)
unnamed: C66.1, J81.1, JP27.1 (IN)
unnamed: C70.1, J83.1, JP31.1 (IN)
unnamed: C71.1, J84.1, JP32.1 (IN)
unnamed: C72.1, J85.1, JP33.1 (IN)
unnamed: C75.1, J86.1, JP36.1 (IN)
unnamed: C76.1, J87.1, JP37.1 (IN)
unnamed: D18.1 (K), F2.2, Q6.3 (D)
unnamed: D18.2 (A), R63.2
unnamed: D19.1 (K), F3.2, Q7.3 (D)
unnamed: D19.2 (A), R64.2
unnamed: D25.1 (K), F4.2, Q11.3 (D)
unnamed: D25.2 (A), R77.2
unnamed: D26.1 (K), LS1.1, R78.2
unnamed: D26.2 (A), LS1.2, Q14.3 (D)
unnamed: F2.1, J82.1
unnamed: F3.1, J82.3
unnamed: F4.1, J88.1
unnamed: J79.3, JP22.1 (A), Q3.3 (D)
unnamed: J80.3, JP23.1 (A), Q4.3 (D)
unnamed: J81.3, JP24.1 (A), Q5.3 (D)
unnamed: J83.3, JP28.1 (A), Q8.3 (D)
unnamed: J84.3, JP29.1 (A), Q9.3 (D)
unnamed: J85.3, JP30.1 (A), Q10.3 (D)
unnamed: J86.3, JP34.1 (A), Q12.3 (D)
unnamed: J87.3, JP35.1 (A), Q13.3 (D)
unnamed: JP22.2 (C), R55.2
unnamed: JP22.3 (B), Q3.1 (G), R56.2
unnamed: JP23.2 (C), R57.2
unnamed: JP23.3 (B), Q4.1 (G), R58.2
unnamed: JP24.2 (C), R59.2
unnamed: JP24.3 (B), Q5.1 (G), R60.2
unnamed: JP28.2 (C), R65.2
unnamed: JP28.3 (B), Q8.1 (G), R66.2
unnamed: JP29.2 (C), R67.2
unnamed: JP29.3 (B), Q9.1 (G), R68.2
unnamed: JP30.2 (C), R69.2
unnamed: JP30.3 (B), Q10.1 (G), R70.2
unnamed: JP34.2 (C), R71.2
unnamed: JP34.3 (B), Q12.1 (G), R72.2
unnamed: JP35.2 (C), R73.2
unnamed: JP35.3 (B), Q13.1 (G), R74.2
unnamed: Q6.2 (G), R62.1
unnamed: Q7.2 (G), R61.1
unnamed: Q11.2 (G), R75.1
unnamed: Q14.1 (G), R76.1
unnamed: R61.2, U7.7 (OUT_A)
unnamed: R62.2, U7.5 (OUT_B)
unnamed: R75.2, U8.7 (OUT_A)

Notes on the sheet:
Medium Power Outputs
High Power Outputs
Buzzer
